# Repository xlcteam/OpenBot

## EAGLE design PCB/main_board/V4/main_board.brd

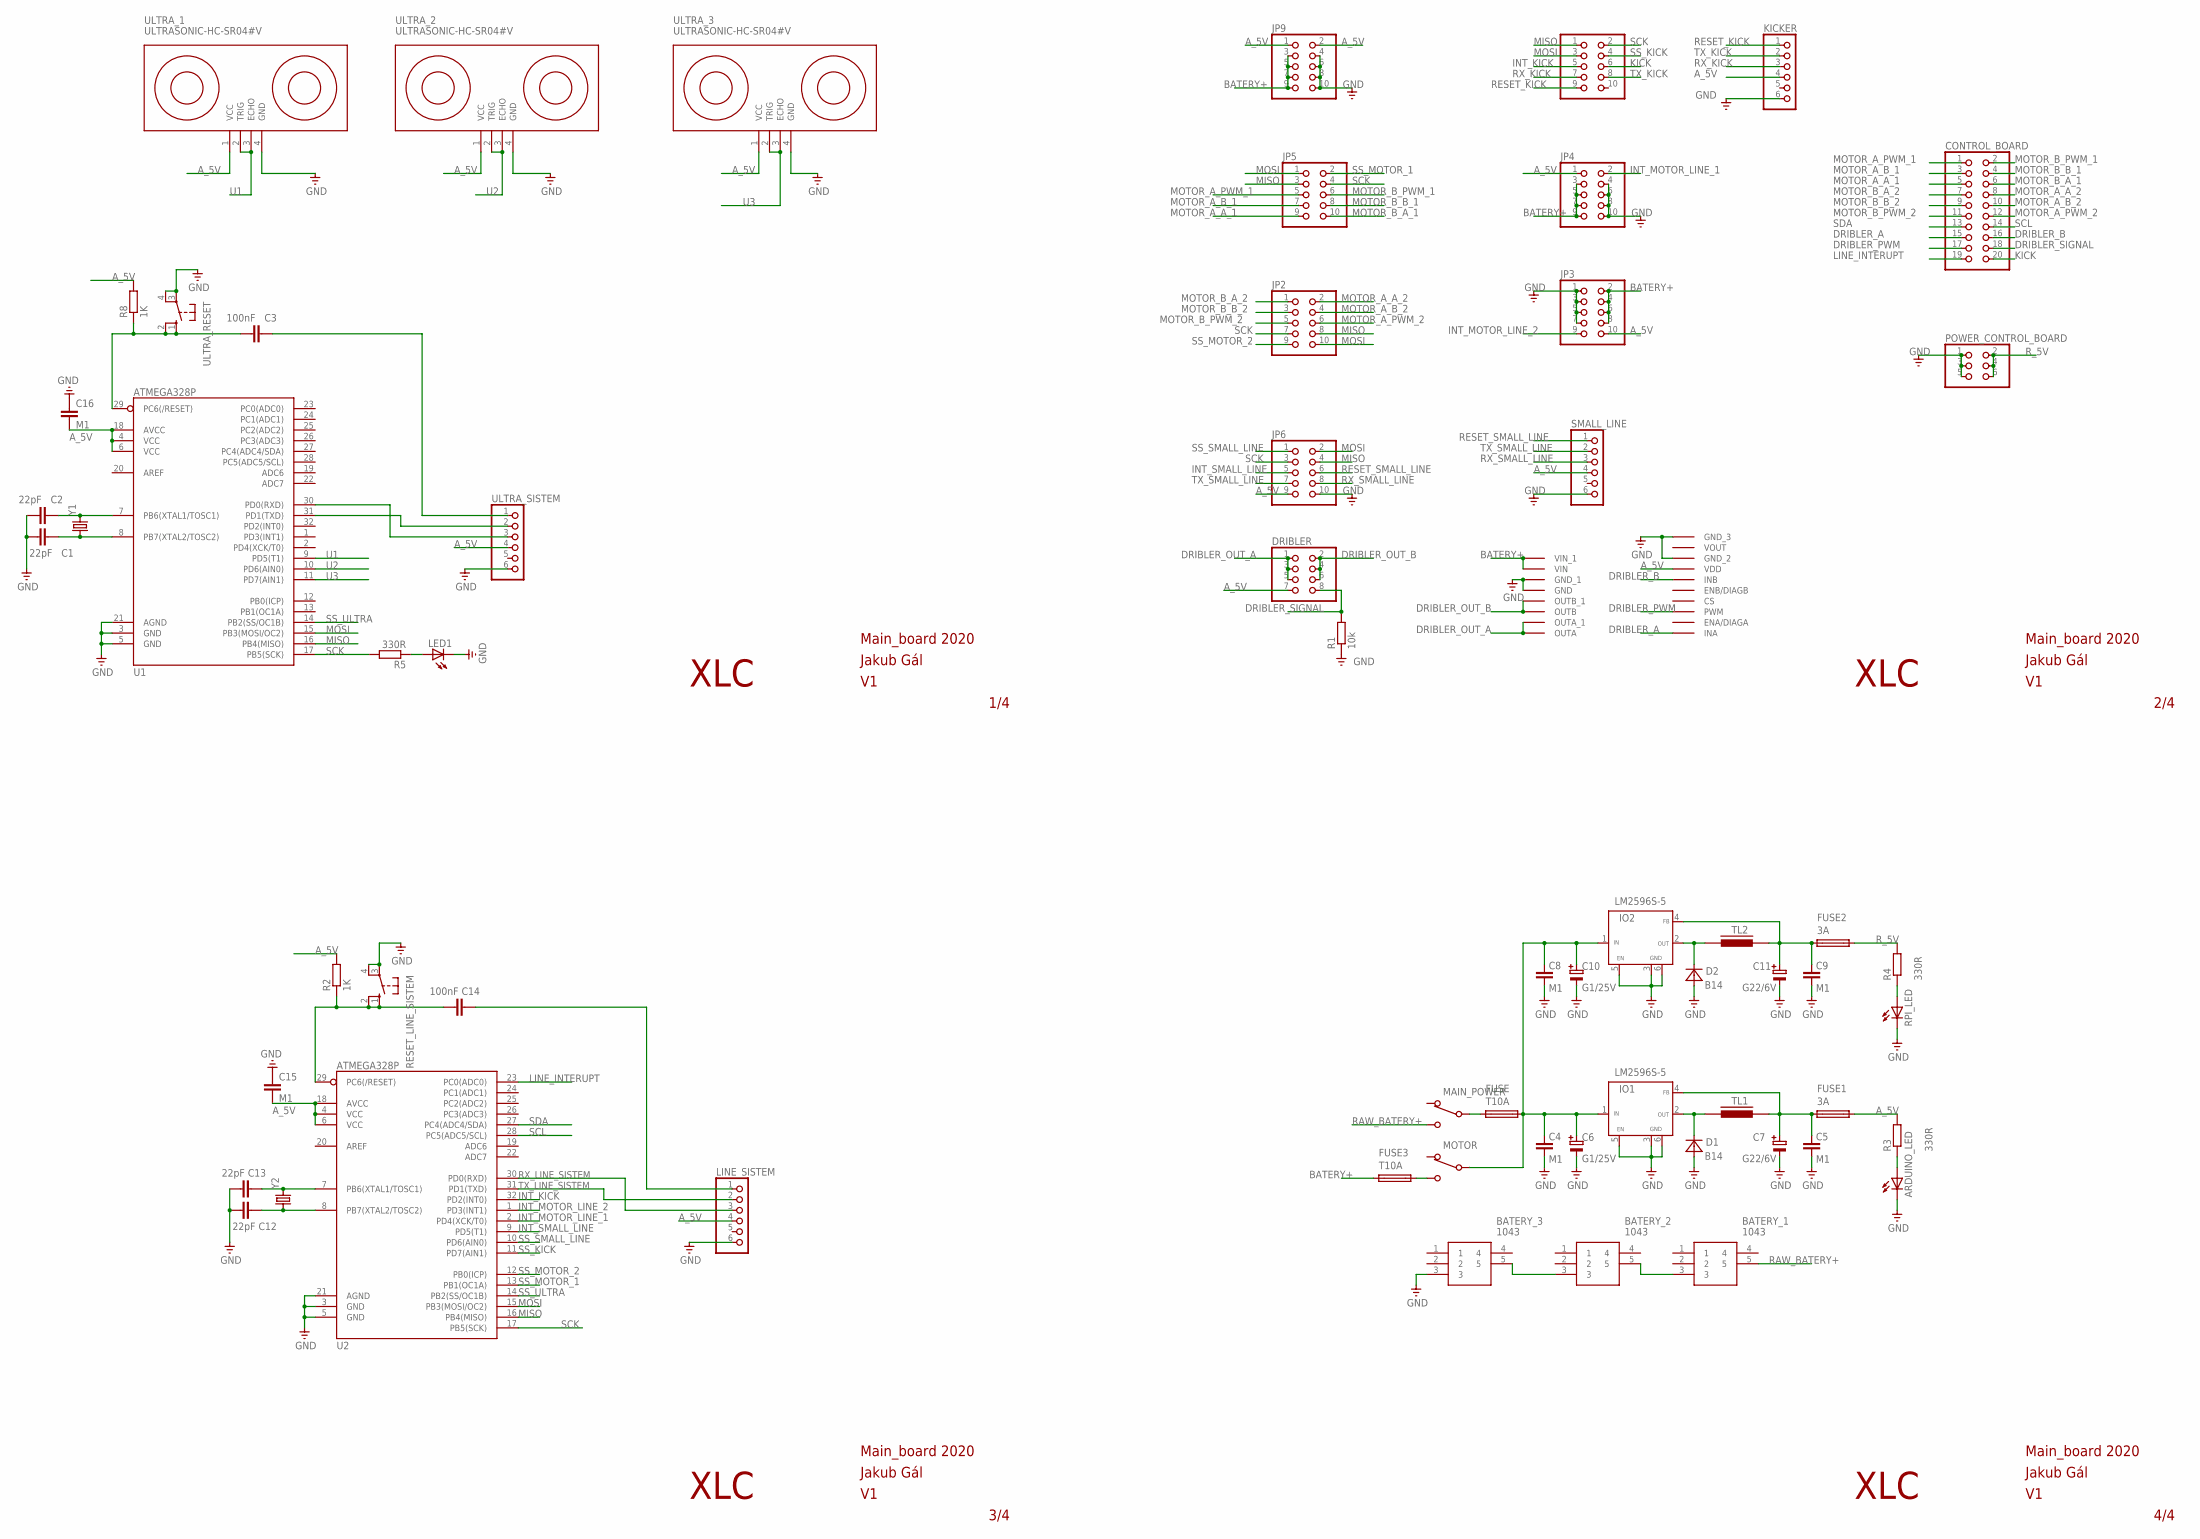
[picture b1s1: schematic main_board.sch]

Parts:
ARDUINO_LED: LEDCHIPLED_0603; CHIPLED_0603
BATERY_1, BATERY_2, BATERY_3: 1043
C1, C2, C12, C13: 22pF; C0603
C3, C14: 100nF; C0603
C4, C5, C8, C9: M1; SMD-1206
C6, C10: G1/25V; SMD-ELE-D
C7, C11: G22/6V; SMD-ELE-D
C15, C16: M1; C0603
CONTROL_BOARD: PINHD-2X10_2.54-SMD; 2X10SMD
D1, D2: B14; D-3,6X5,5
DRIBLER: PINHD-2X4_2.54-SMD; 2X04SMD
FUSE, FUSE3: T10A; SH22,5A
FUSE1, FUSE2: 3A; SH22,5A
IO1, IO2: LM2596S-5; TO263-5
JP2, JP3, JP4, JP5, JP6, JP8, JP9: PINHD-2X5_2.54-SMD; 2X05SMD
KICKER: PINHD-1X6; 1X06
LED1: LEDCHIPLED_0603; CHIPLED_0603
LINE_SISTEM: PINHD-1X6; 1X06
MAIN_POWER: PREP-1PB; P-B069B
MOTOR: PREP-1PB; P-B069B
POWER_CONTROL_BOARD: PINHD-2X3_2.54-SMD; 2X03SMD
R1: 10k; R0603
R2, R8: 1K; R0603
R3, R4, R5: 330R; R0603
RESET_LINE_SISTEM: 10-XX; B3F-10XX
RPI_LED: LEDCHIPLED_0603; CHIPLED_0603
SMALL_LINE: PINHD-1X6; 1X06
TL1, TL2: INDUK-TLSMD1; INDUK-TL
U1, U2: ATMEGA328P; TQFP32-08
U$4: MOTOR_DRIVER
ULTRA_1, ULTRA_2, ULTRA_3: ULTRASONIC-HC-SR04#V
ULTRA_RESET: 10-XX; B3F-10XX
ULTRA_SISTEM: PINHD-1X6; 1X06
Y1, Y2: CRYSTALHC49US; HC49US

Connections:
A_5V: C15.2, C16.2, DRIBLER.7, FUSE1.2, JP3.10, JP4.1, JP6.9, JP9.1, JP9.2, KICKER.4, LINE_SISTEM.4, R2.2, R3.2, R8.2, SMALL_LINE.4, U1.4 (VCC), U1.6 (VCC), U1.18 (AVCC), U2.4 (VCC), U2.6 (VCC), U2.18 (AVCC), U$4.VDD, ULTRA_1.1 (VCC), ULTRA_2.1 (VCC), ULTRA_3.1 (VCC), ULTRA_SISTEM.4
BATERY+: FUSE3.1, JP3.2, JP3.4, JP3.6, JP3.8, JP4.3, JP4.5, JP4.7, JP4.9, JP9.3, JP9.5, JP9.7, JP9.9, U$4.VIN, U$4.VIN_1
DRIBLER_A: CONTROL_BOARD.15, U$4.INA
DRIBLER_B: CONTROL_BOARD.16, U$4.INB
DRIBLER_OUT_A: DRIBLER.1, DRIBLER.3, DRIBLER.5, U$4.OUTA, U$4.OUTA_1
DRIBLER_OUT_B: DRIBLER.2, DRIBLER.4, DRIBLER.6, U$4.OUTB, U$4.OUTB_1
DRIBLER_PWM: CONTROL_BOARD.17, U$4.PWM
DRIBLER_SIGNAL: CONTROL_BOARD.18, DRIBLER.8, R1.2
GND: ARDUINO_LED.C, BATERY_3.3, C1.1, C2.1, C4.1, C5.1, C6.MINUS, C7.MINUS, C8.1, C9.1, C10.MINUS, C11.MINUS, C12.1, C13.1, C15.1, C16.1, D1.A, D2.A, IO1.3 (GND), IO1.5 (EN), IO1.6 (GND), IO2.3 (GND), IO2.5 (EN), IO2.6 (GND), JP3.1, JP3.3, JP3.5, JP3.7, JP4.4, JP4.6, JP4.8, JP4.10, JP6.10, JP9.4, JP9.6, JP9.8, JP9.10, KICKER.6, LED1.C, LINE_SISTEM.6, POWER_CONTROL_BOARD.1, POWER_CONTROL_BOARD.3, POWER_CONTROL_BOARD.5, R1.1, RESET_LINE_SISTEM.3, RESET_LINE_SISTEM.4 (P1), RPI_LED.C, SMALL_LINE.6, U1.3 (GND), U1.5 (GND), U1.21 (AGND), U2.3 (GND), U2.5 (GND), U2.21 (AGND), U$4.GND, U$4.GND_1, U$4.GND_2, U$4.GND_3, ULTRA_1.4 (GND), ULTRA_2.4 (GND), ULTRA_3.4 (GND), ULTRA_RESET.3, ULTRA_RESET.4 (P1), ULTRA_SISTEM.6
INT_KICK: JP8.5, U2.32 (PD2(INT0))
INT_MOTOR_LINE_1: JP4.2, U2.2 (PD4(XCK/T0))
INT_MOTOR_LINE_2: JP3.9, U2.1 (PD3(INT1))
INT_SMALL_LINE: JP6.5, U2.9 (PD5(T1))
KICK: CONTROL_BOARD.20, JP8.6
LINE_INTERUPT: CONTROL_BOARD.19, U2.23 (PC0(ADC0))
MISO: JP2.8, JP5.3, JP6.4, JP8.1, U1.16 (PB4(MISO)), U2.16 (PB4(MISO))
MOSI: JP2.10, JP5.1, JP6.2, JP8.3, U1.15 (PB3(MOSI/OC2)), U2.15 (PB3(MOSI/OC2))
MOTOR_A_A_1: CONTROL_BOARD.5, JP5.9
MOTOR_A_A_2: CONTROL_BOARD.8, JP2.2
MOTOR_A_B_1: CONTROL_BOARD.3, JP5.7
MOTOR_A_B_2: CONTROL_BOARD.10, JP2.4
MOTOR_A_PWM_1: CONTROL_BOARD.1, JP5.5
MOTOR_A_PWM_2: CONTROL_BOARD.12, JP2.6
MOTOR_B_A_1: CONTROL_BOARD.6, JP5.10
MOTOR_B_A_2: CONTROL_BOARD.7, JP2.1
MOTOR_B_B_1: CONTROL_BOARD.4, JP5.8
MOTOR_B_B_2: CONTROL_BOARD.9, JP2.3
MOTOR_B_PWM_1: CONTROL_BOARD.2, JP5.6
MOTOR_B_PWM_2: CONTROL_BOARD.11, JP2.5
unnamed: BATERY_1.3, BATERY_2.5
unnamed: BATERY_2.3, BATERY_3.5
unnamed: D2.K, IO2.2 (OUT), TL2.1
unnamed: FUSE.1, MAIN_POWER.2 (2-COM)
unnamed: C13.2, U2.7 (PB6(XTAL1/TOSC1)), Y2.2
unnamed: D1.K, IO1.2 (OUT), TL1.1
unnamed: C2.2, U1.7 (PB6(XTAL1/TOSC1)), Y1.2
unnamed: C1.2, U1.8 (PB7(XTAL2/TOSC2)), Y1.1
unnamed: C12.2, U2.8 (PB7(XTAL2/TOSC2)), Y2.1
unnamed: C5.2, C7.PLUS, FUSE1.1, IO1.4 (FB), TL1.2
unnamed: C14.2, LINE_SISTEM.1
unnamed: C14.1, R2.1, RESET_LINE_SISTEM.1 (S), RESET_LINE_SISTEM.2 (S1), U2.29 (PC6(/RESET))
unnamed: C4.2, C6.PLUS, C8.2, C10.PLUS, FUSE.2, IO1.1 (IN), IO2.1 (IN), MOTOR.2 (2-COM)
unnamed: FUSE3.2, MOTOR.1 (1-OFF)
unnamed: U1.30 (PD0(RXD)), ULTRA_SISTEM.3
unnamed: U1.31 (PD1(TXD)), ULTRA_SISTEM.2
unnamed: C3.2, ULTRA_SISTEM.1
unnamed: C3.1, R8.1, U1.29 (PC6(/RESET)), ULTRA_RESET.1 (S), ULTRA_RESET.2 (S1)
unnamed: LED1.A, R5.1
unnamed: C9.2, C11.PLUS, FUSE2.1, IO2.4 (FB), TL2.2
unnamed: ARDUINO_LED.A, R3.1
unnamed: R4.1, RPI_LED.A
RAW_BATERY+: BATERY_1.5, MAIN_POWER.1 (1-OFF)
RESET_KICK: JP8.9, KICKER.1
RESET_SMALL_LINE: JP6.6, SMALL_LINE.1
RX_KICK: JP8.7, KICKER.3
RX_LINE_SISTEM: LINE_SISTEM.3, U2.30 (PD0(RXD))
RX_SMALL_LINE: JP6.8, SMALL_LINE.3
R_5V: FUSE2.2, POWER_CONTROL_BOARD.2, POWER_CONTROL_BOARD.4, POWER_CONTROL_BOARD.6, R4.2
SCK: JP2.7, JP5.4, JP6.3, JP8.2, R5.2, U1.17 (PB5(SCK)), U2.17 (PB5(SCK))
SCL: CONTROL_BOARD.14, U2.28 (PC5(ADC5/SCL))
SDA: CONTROL_BOARD.13, U2.27 (PC4(ADC4/SDA))
SS_KICK: JP8.4, U2.11 (PD7(AIN1))
SS_MOTOR_1: JP5.2, U2.13 (PB1(OC1A))
SS_MOTOR_2: JP2.9, U2.12 (PB0(ICP))
SS_SMALL_LINE: JP6.1, U2.10 (PD6(AIN0))
SS_ULTRA: U1.14 (PB2(SS/OC1B)), U2.14 (PB2(SS/OC1B))
TX_KICK: JP8.8, KICKER.2
TX_LINE_SISTEM: LINE_SISTEM.2, U2.31 (PD1(TXD))
TX_SMALL_LINE: JP6.7, SMALL_LINE.2
U1: U1.9 (PD5(T1)), ULTRA_1.2 (TRIG), ULTRA_1.3 (ECHO)
U2: U1.10 (PD6(AIN0)), ULTRA_2.2 (TRIG), ULTRA_2.3 (ECHO)
U3: U1.11 (PD7(AIN1)), ULTRA_3.2 (TRIG), ULTRA_3.3 (ECHO)

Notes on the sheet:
1/4
2/4
3/4
4/4
XLC
Main_board 2020
Jakub Gál

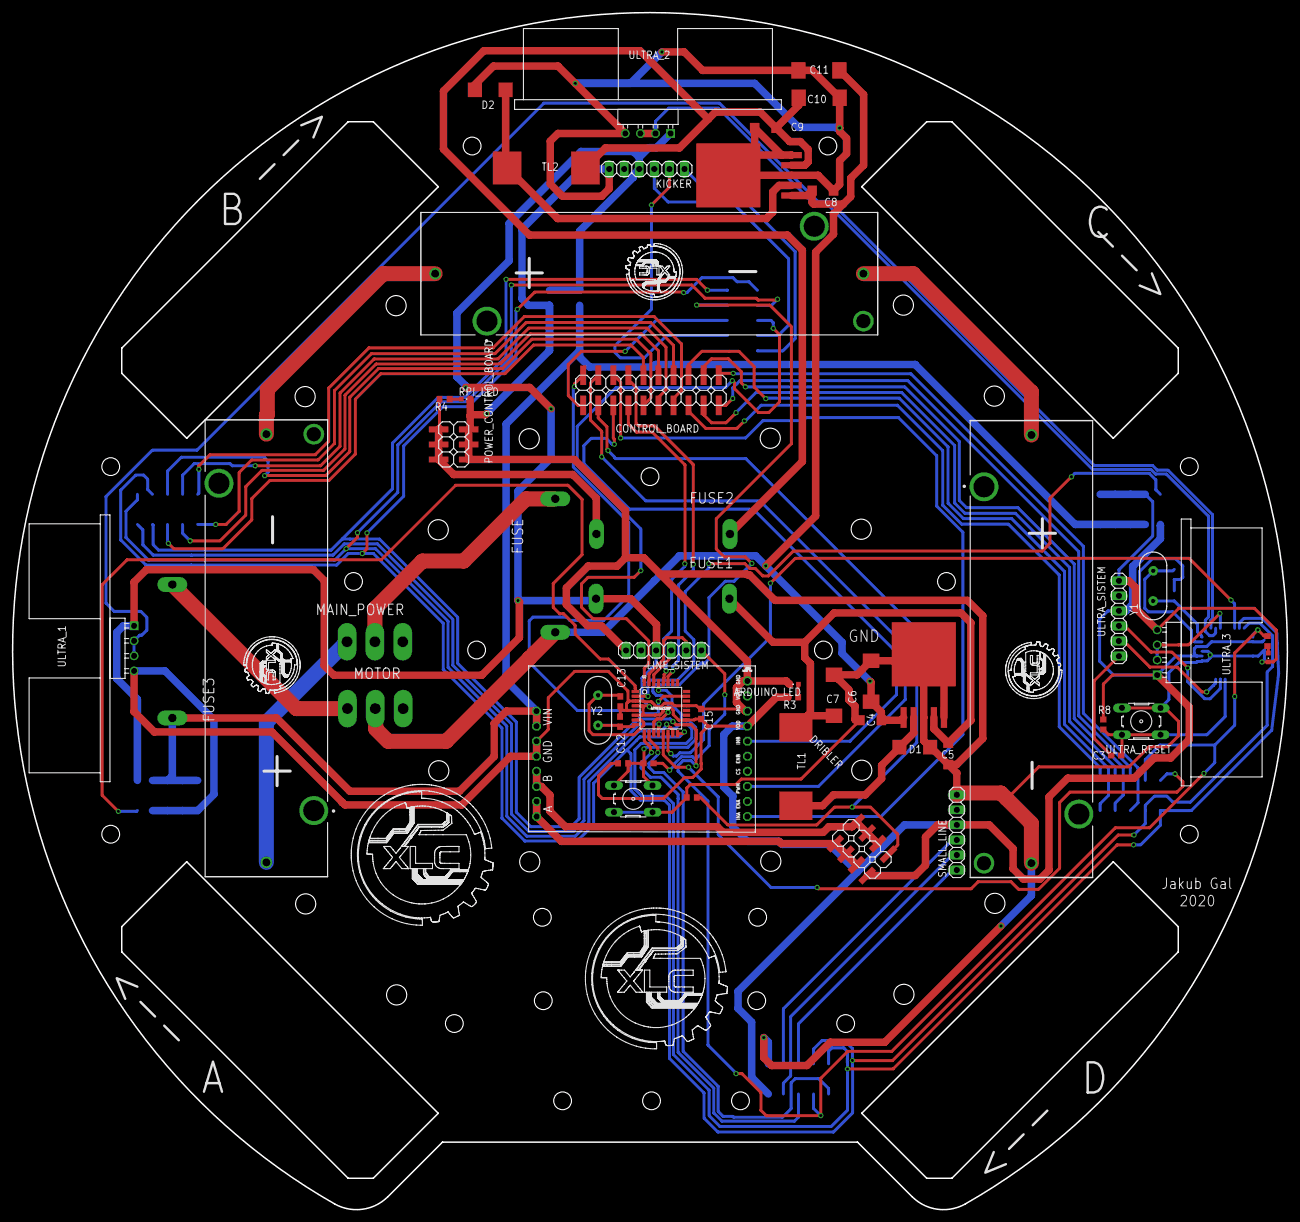
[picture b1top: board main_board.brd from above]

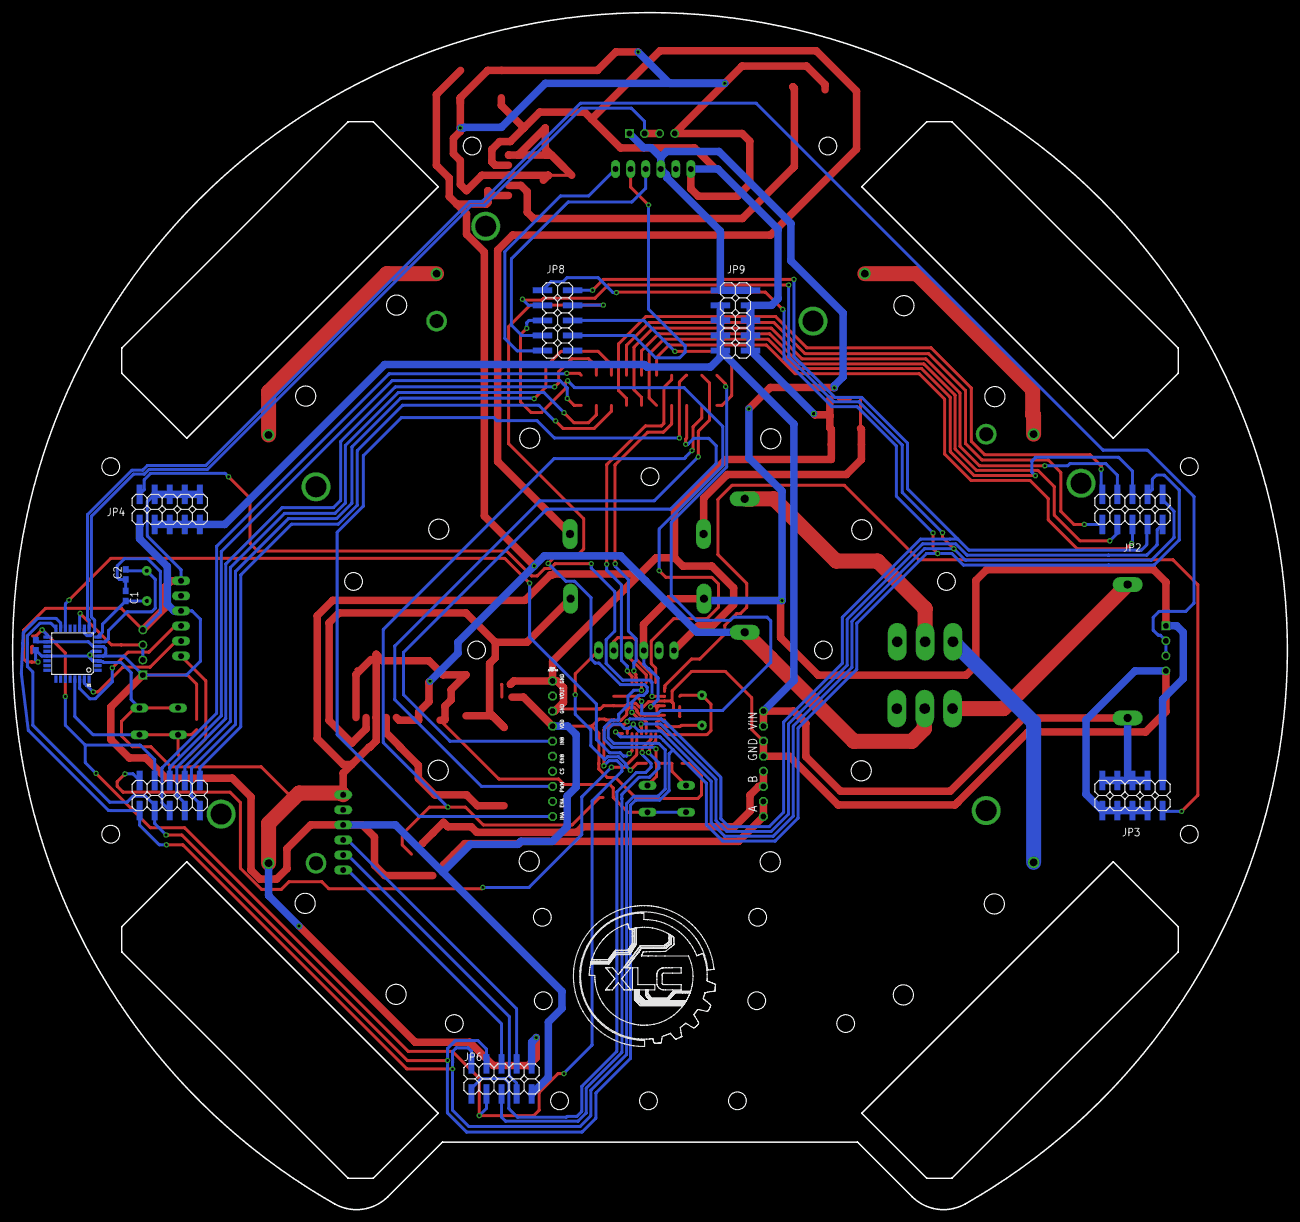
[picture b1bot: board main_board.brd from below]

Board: 2 copper layers, 215.0 x 201.9 mm, 64 parts (11 on the bottom side), 72 nets.

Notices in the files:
parts and their libraries:
diy-modules: Released under the Creative Commons Attribution 4.0 International License: http://creativecommons.org/licenses/by/4.0
SparkFun-DigitalIC: Licensing: CC v3.0 Share-Alike You are welcome to use this library for commercial purposes.
